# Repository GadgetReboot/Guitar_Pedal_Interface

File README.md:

# Guitar_Pedal_Interface
<br><br><BR><BR>
Guitar jacks, stomp switch, pots, toggle switches and a -9v supply generator from +9v in for guitar effect prototyping.

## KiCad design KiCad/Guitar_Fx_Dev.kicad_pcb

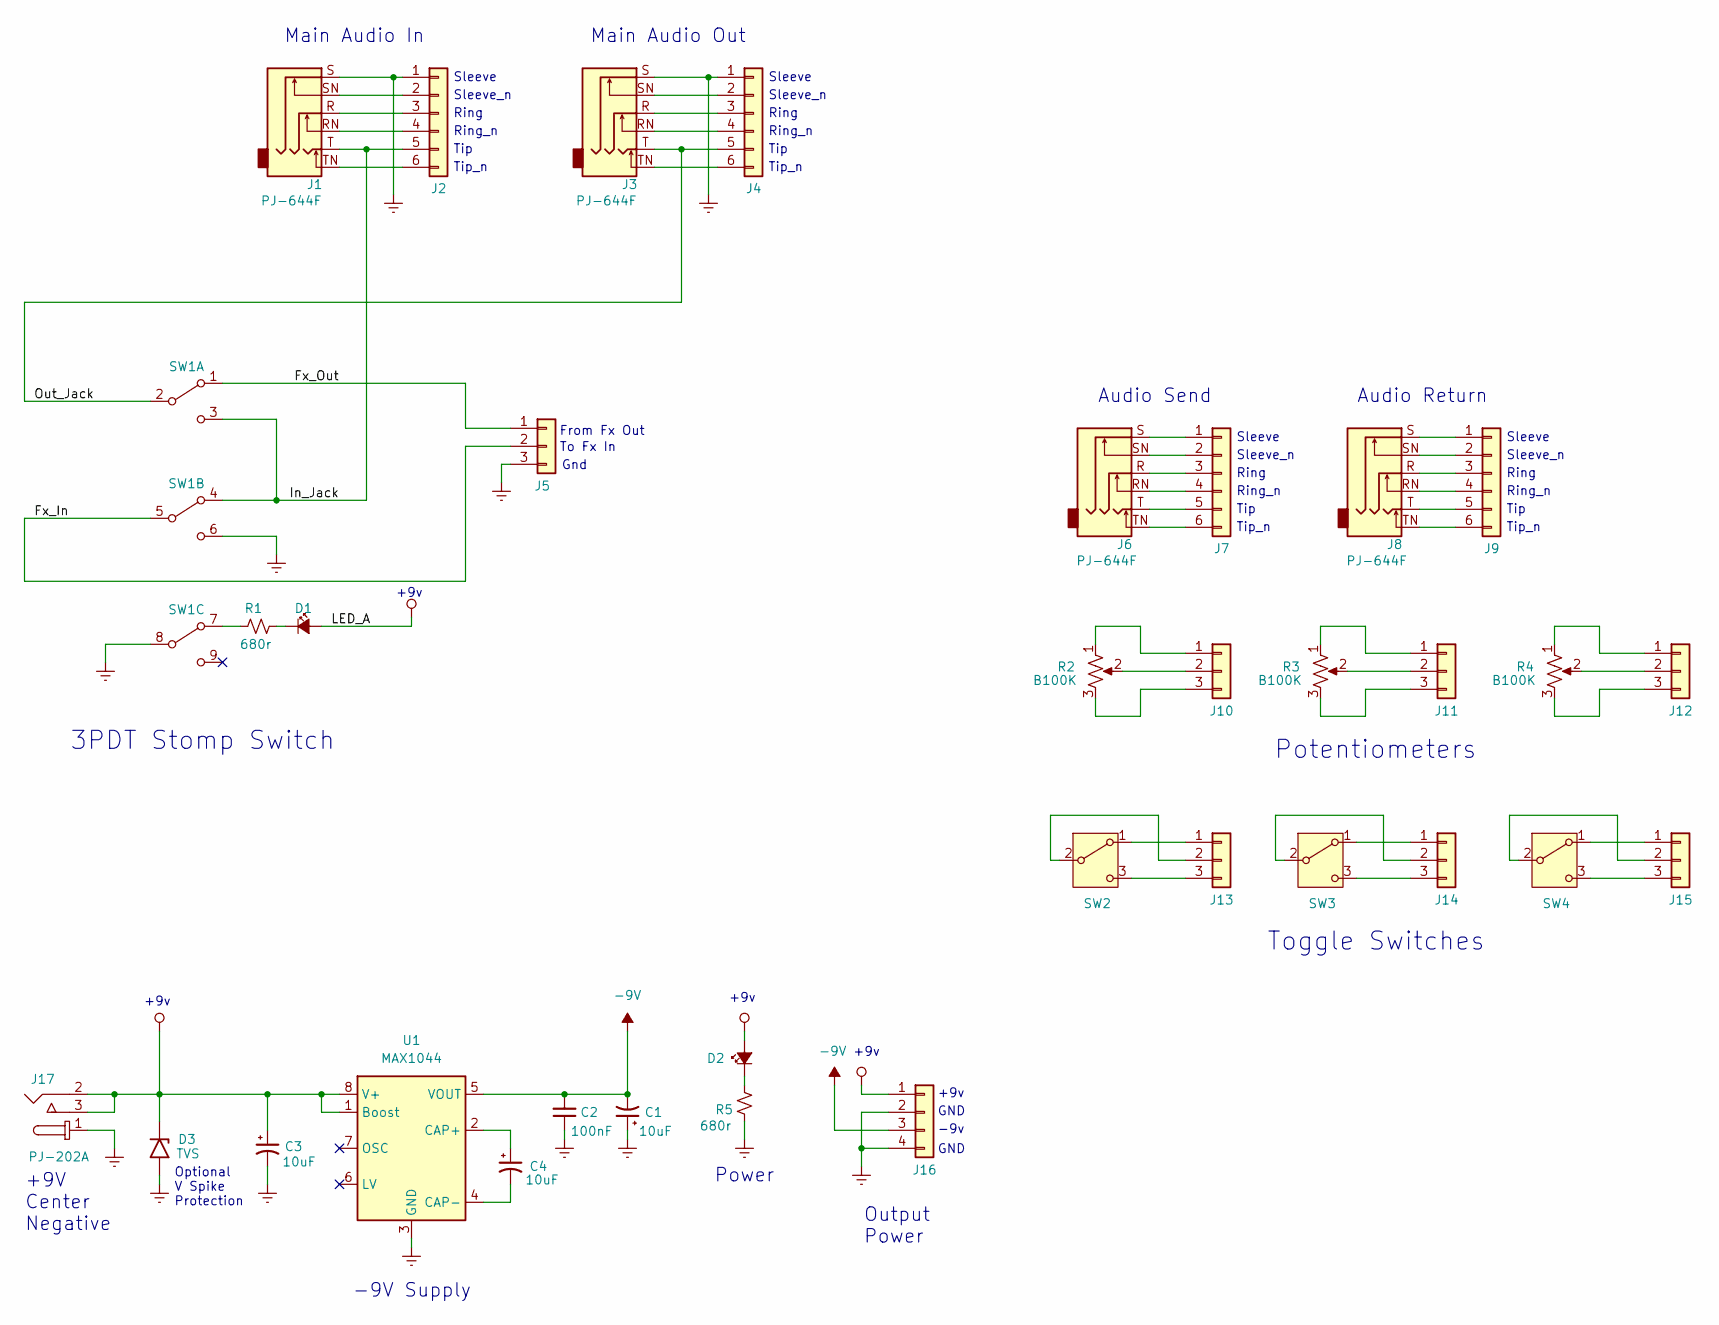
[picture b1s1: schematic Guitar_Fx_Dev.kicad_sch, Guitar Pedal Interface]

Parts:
C1, C3, C4: 10uF; CP_Radial_D5.0mm_P2.50mm
C2: 100nF; C_Disc_D4.7mm_W2.5mm_P5.00mm
D1, D2: LED_Small_ALT; LED_D5.0mm
D3: TVS; D_DO-15_P12.70mm_Horizontal
J1, J3, J6, J8: PJ-644F; Jack_6.35mm_Neutrik_NMJ6HFD2_Horizontal
J2, J4, J7, J9: Conn_01x06; PinHeader_1x06_P2.54mm_Vertical
J5, J10, J11, J12, J13, J14, J15: Conn_01x03; PinHeader_1x03_P2.54mm_Vertical
J16: Conn_01x04; PinHeader_1x04_P2.54mm_Vertical
J17: PJ-202A; Barrel_Jack_5.5mmODx2.1mmID_PJ-202A; MPN PJ-202A; Digi-Key_PN CP-202A-ND
R1, R5: 680r; R_Axial_DIN0207_L6.3mm_D2.5mm_P10.16mm_Horizontal
R2, R3, R4: B100K; Potentiometer_Vimex
SW1: SW_3PDT; STOMP-SWITCH-3PDT
SW2, SW3, SW4: Adam Tech SW-T2-2E-A-A2-M1; Toggle_Sw_SPDT
U1: MAX1044; DIP-8_W7.62mm

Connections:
-9V: C1.2, C2.2, J16.3, U1.5 (VOUT)
/Fx_In: J5.2, SW1.5 (B)
/Fx_Out: J5.1, SW1.1 (A)
/In_Jack: J1.T, J2.5, SW1.3 (C), SW1.4 (A)
/Out_Jack: J3.T, J4.5, SW1.2 (B)
GNDREF: C1.1, C2.1, C3.2, D3.2 (A2), J1.S, J2.1, J3.S, J4.1, J5.3, J16.2, J16.4, J17.1, R5.2, SW1.6 (C), SW1.8 (B), U1.3 (GND)
unnamed: D1.1 (K), R1.1
unnamed: D2.1 (K), R5.1
unnamed: J1.SN, J2.2
unnamed: J1.R, J2.3
unnamed: J1.RN, J2.4
unnamed: J1.TN, J2.6
unnamed: J3.SN, J4.2
unnamed: J3.R, J4.3
unnamed: J3.RN, J4.4
unnamed: J3.TN, J4.6
unnamed: J6.S, J7.1
unnamed: J6.SN, J7.2
unnamed: J6.R, J7.3
unnamed: J6.RN, J7.4
unnamed: J6.T, J7.5
unnamed: J6.TN, J7.6
unnamed: J8.S, J9.1
unnamed: J8.SN, J9.2
unnamed: J8.R, J9.3
unnamed: J8.RN, J9.4
unnamed: J8.T, J9.5
unnamed: J8.TN, J9.6
unnamed: J10.1, R2.1
unnamed: J10.2, R2.2
unnamed: J10.3, R2.3
unnamed: J11.1, R3.1
unnamed: J11.2, R3.2
unnamed: J11.3, R3.3
unnamed: J12.1, R4.1
unnamed: J12.2, R4.2
unnamed: J12.3, R4.3
unnamed: J13.1, SW2.1 (A)
unnamed: J13.2, SW2.2 (B)
unnamed: J13.3, SW2.3 (C)
unnamed: J14.1, SW3.1 (A)
unnamed: J14.2, SW3.2 (B)
unnamed: J14.3, SW3.3 (C)
unnamed: J15.1, SW4.1 (A)
unnamed: J15.2, SW4.2 (B)
unnamed: J15.3, SW4.3 (C)
unnamed: R1.2, SW1.7 (A)
unnamed: C4.1, U1.2 (CAP+)
unnamed: C4.2, U1.4 (CAP-)
VCC: C3.1, D1.2 (A), D2.2 (A), D3.1 (A1), J16.1, J17.2, J17.3, U1.1 (Boost), U1.8 (V+)

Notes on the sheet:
Sleeve_n
+9v
Output Power
Toggle Switches
Ring_n
Ring
To Fx In
Sleeve
Potentiometers
Power
-9V Supply
Tip_n
3PDT Stomp Switch
Audio Send
From Fx Out
Gnd
GND
Tip
-9v
Main Audio In
Optional V Spike Protection
+9V Center Negative
Main Audio Out
Audio Return

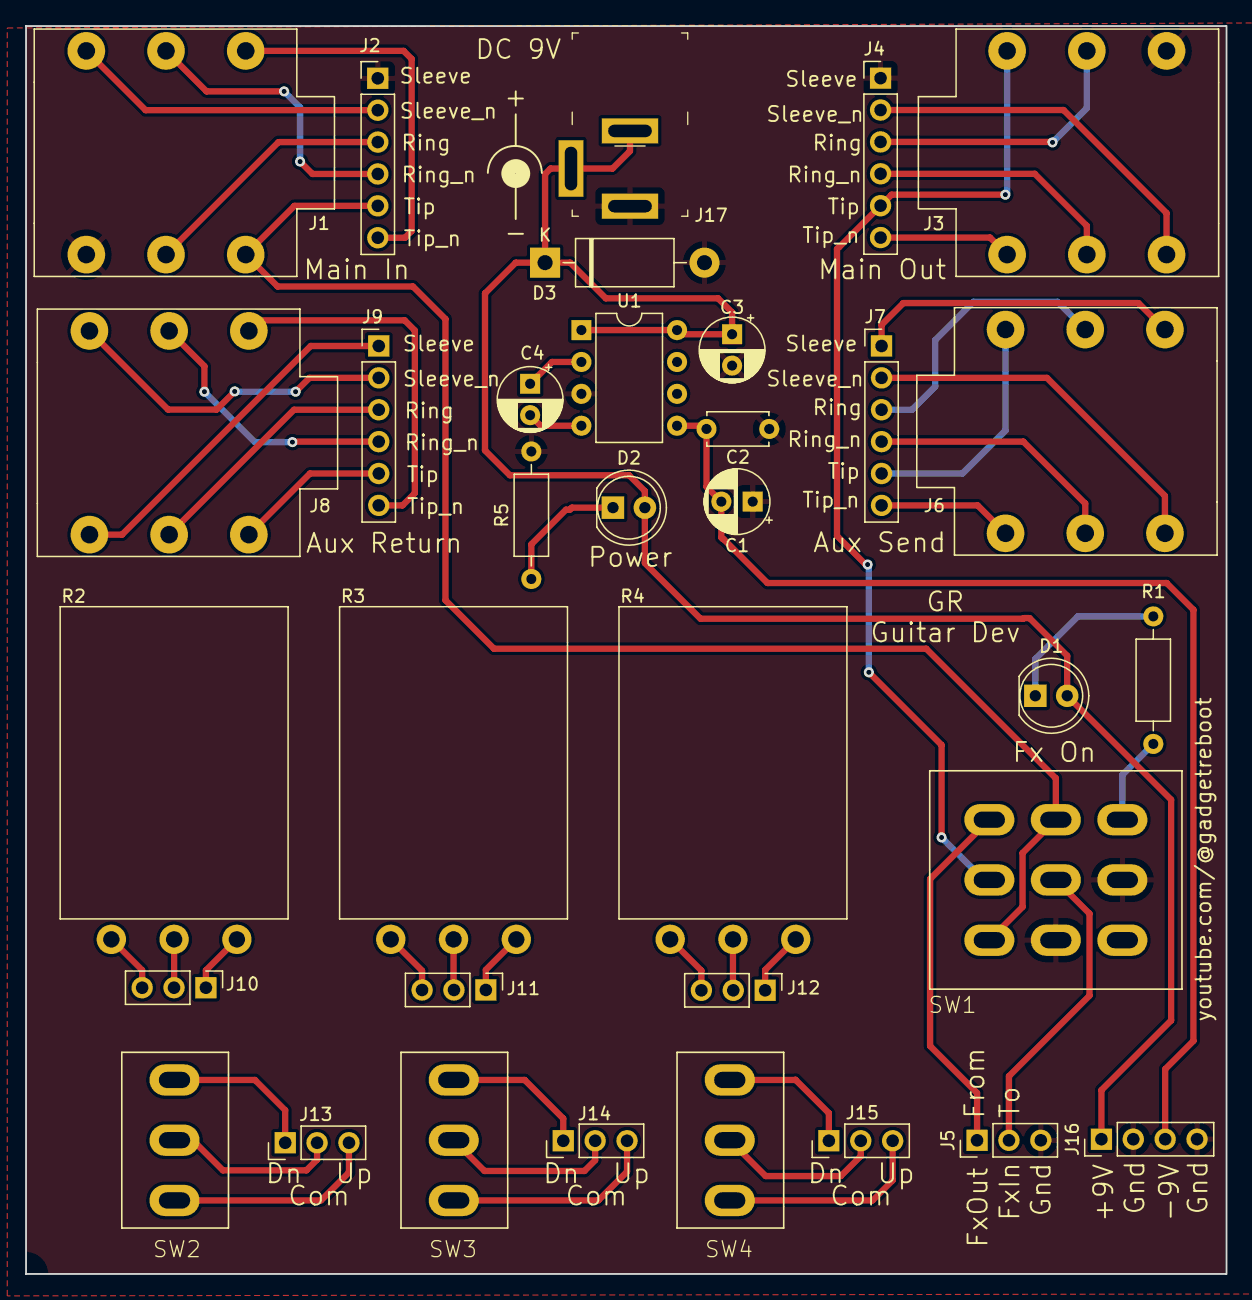
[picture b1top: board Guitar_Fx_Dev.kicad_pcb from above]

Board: 2 copper layers, 95.6 x 99.4 mm, 34 parts (0 on the bottom side), 50 nets.
